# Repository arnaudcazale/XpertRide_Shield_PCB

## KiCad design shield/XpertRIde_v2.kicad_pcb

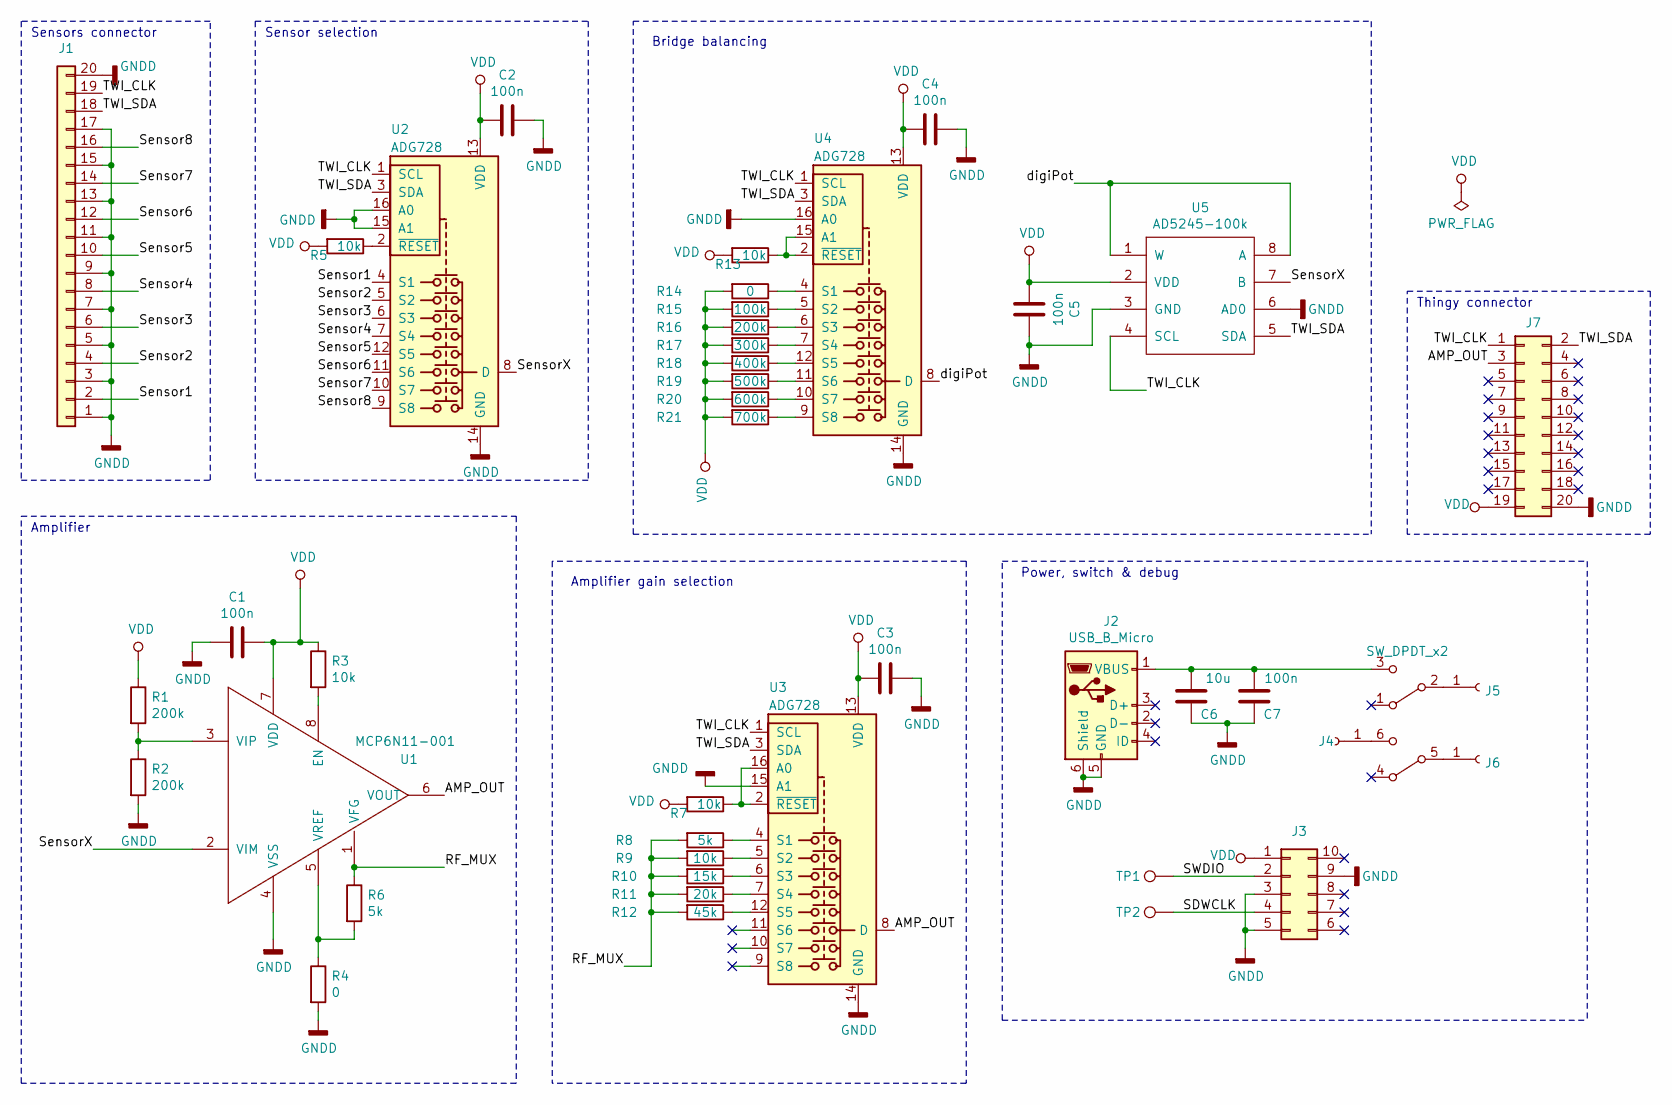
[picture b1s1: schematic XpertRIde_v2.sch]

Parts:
C1, C2, C3, C4, C5, C7: 100n; C_0402
C6: 10u; C_0603
J1: Conn_01x20; Samtec_ESHF_20
J2: USB_B_Micro; CUI_UJ2-MIBH-4-SMT-TR-67
J3: Conn_02x05_Counter_Clockwise; Tag_Connect_10
J4, J5, J6: Conn_01x01_Female; SolderWirePad_single_0-8mmDrill
J7: Conn_02x10_Odd_Even; Pin_Header_Straight_2x10_Pitch2.54mm
R1, R2, R16: 200k; R_0402
R3, R5, R7, R9, R13: 10k; R_0402
R4, R14: 0; R_0402
R6, R8: 5k; R_0402
R10: 15k; R_0402
R11: 20k; R_0402
R12: 45k; R_0402
R15: 100k; R_0402
R17: 300k; R_0402
R18: 400k; R_0402
R19: 500k; R_0402
R20: 600k; R_0402
R21: 700k; R_0402
SW1: SW_DPDT_x2; DPDT_IP67
TP1, TP2: TestPoint; Measurement_Point_Round-SMD-Pad_Small
U1: MCP6N11-001; SOIC-8_3.9x4.9mm_Pitch1.27mm
U2, U3, U4: ADG728; TSSOP-16_4.4x5mm_P0.65mm
U5: AD5245-100k; SOT-23-8

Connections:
/AMP_OUT: J7.3, U1.6 (VOUT), U3.8 (D)
/RF_MUX: R6.1, R8.2, R9.2, R10.2, R11.2, R12.2, U1.1 (VFG)
/SDWCLK: J3.4, TP2.1
/SWDIO: J3.2, TP1.1
/Sensor1: J1.2, U2.4 (S1)
/Sensor2: J1.4, U2.5 (S2)
/Sensor3: J1.6, U2.6 (S3)
/Sensor4: J1.8, U2.7 (S4)
/Sensor5: J1.10, U2.12 (S5)
/Sensor6: J1.12, U2.11 (S6)
/Sensor7: J1.14, U2.10 (S7)
/Sensor8: J1.16, U2.9 (S8)
/SensorX: U1.2 (VIM), U2.8 (D), U5.7 (B)
/TWI_CLK: J1.19, J7.1, U2.1 (SCL), U3.1 (SCL), U4.1 (SCL), U5.4 (SCL)
/TWI_SDA: J1.18, J7.2, U2.3 (SDA), U3.3 (SDA), U4.3 (SDA), U5.5 (SDA)
/digiPot: U4.8 (D), U5.1 (W), U5.8 (A)
GNDD: C1.2, C2.1, C3.1, C4.1, C5.1, C6.1, C7.1, J1.1, J1.3, J1.5, J1.7, J1.9, J1.11, J1.13, J1.15, J1.17, J1.20, J2.5 (GND), J2.6 (Shield), J3.3, J3.5, J3.9, J7.20, R2.2, R4.2, U1.4 (VSS), U2.14 (GND), U2.15 (A1), U2.16 (A0), U3.14 (GND), U3.15 (A1), U4.14 (GND), U4.16 (A0), U5.3 (GND), U5.6 (AD0)
unnamed: C6.2, C7.2, J2.1 (VBUS), SW1.3 (C)
unnamed: J4.1, SW1.6 (C)
unnamed: J5.1, SW1.2 (B)
unnamed: J6.1, SW1.5 (B)
unnamed: R1.2, R2.1, U1.3 (VIP)
unnamed: R3.2, U1.8 (EN)
unnamed: R4.1, R6.2, U1.5 (VREF)
unnamed: R5.1, U2.2 (~RESET)
unnamed: R7.1, U3.2 (~RESET), U3.16 (A0)
unnamed: R8.1, U3.4 (S1)
unnamed: R9.1, U3.5 (S2)
unnamed: R10.1, U3.6 (S3)
unnamed: R11.1, U3.7 (S4)
unnamed: R12.1, U3.12 (S5)
unnamed: R13.1, U4.2 (~RESET), U4.15 (A1)
unnamed: R14.1, U4.4 (S1)
unnamed: R15.1, U4.5 (S2)
unnamed: R16.1, U4.6 (S3)
unnamed: R17.1, U4.7 (S4)
unnamed: R18.1, U4.12 (S5)
unnamed: R19.1, U4.11 (S6)
unnamed: R20.1, U4.10 (S7)
unnamed: R21.1, U4.9 (S8)
VDD: C1.1, C2.2, C3.2, C4.2, C5.2, J3.1, J7.19, R1.1, R3.1, R5.2, R7.2, R13.2, R14.2, R15.2, R16.2, R17.2, R18.2, R19.2, R20.2, R21.2, U1.7 (VDD), U2.13 (VDD), U3.13 (VDD), U4.13 (VDD), U5.2 (VDD)

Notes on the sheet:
Bridge balancing
Amplifier
Amplifier gain selection
Sensors connector
Sensor selection
Power, switch & debug
Thingy connector

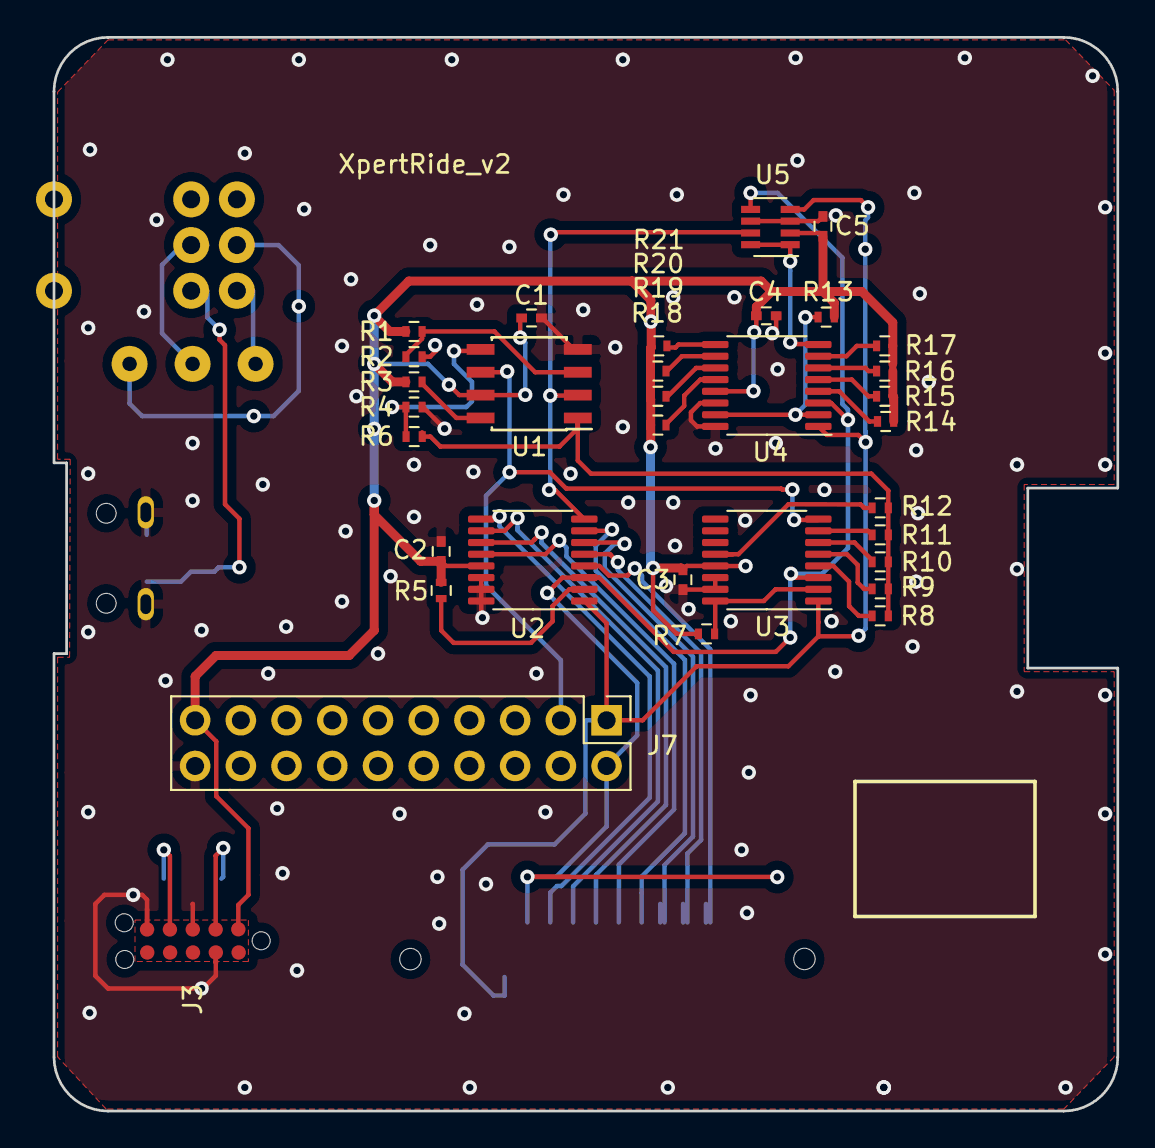
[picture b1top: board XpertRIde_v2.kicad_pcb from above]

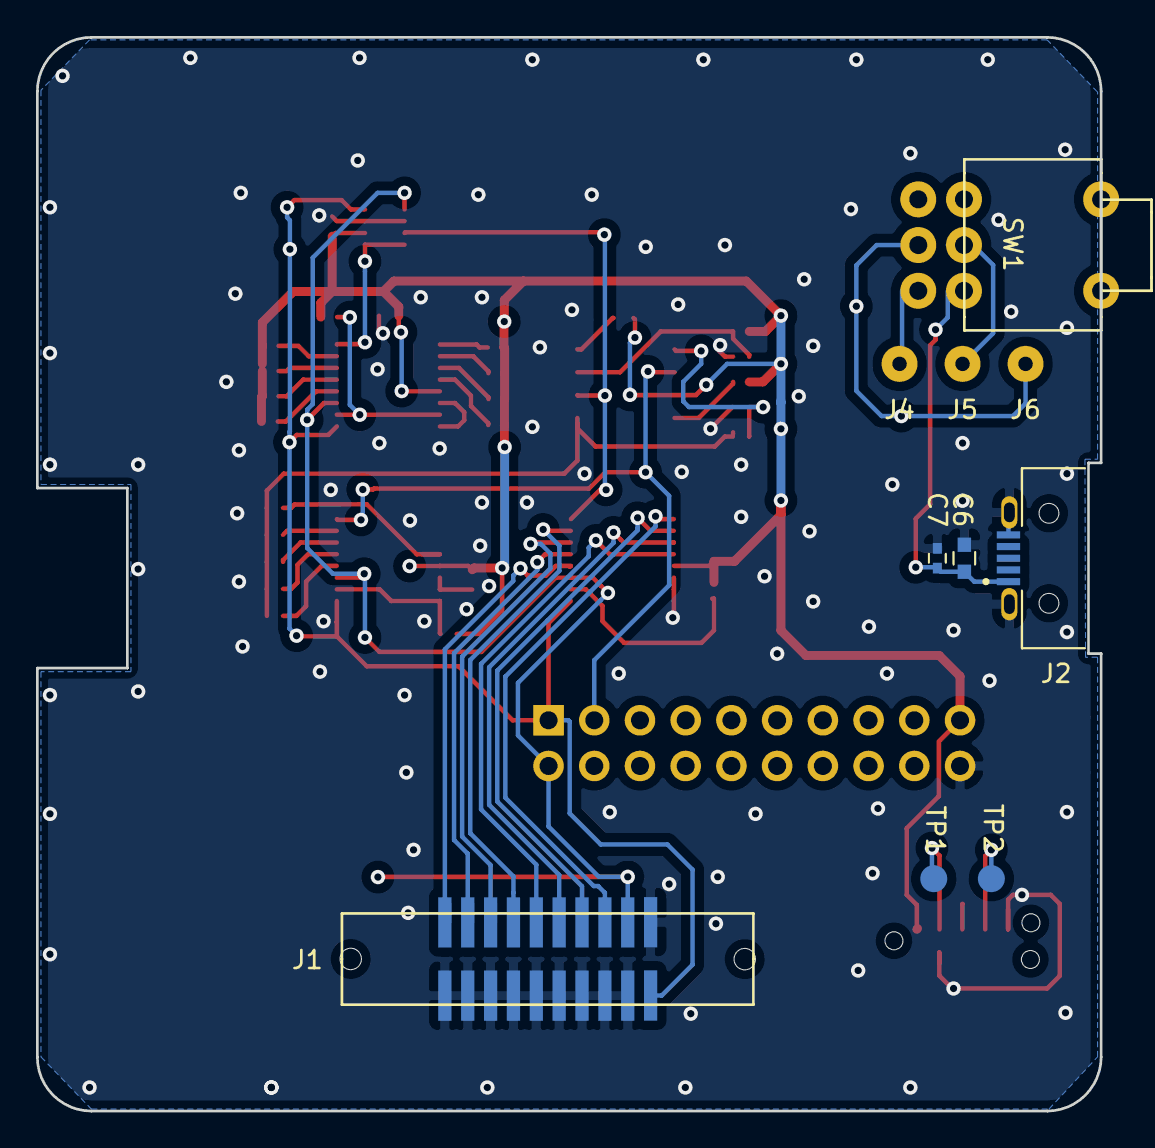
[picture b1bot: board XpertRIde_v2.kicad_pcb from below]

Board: 2 copper layers, 59.1 x 59.7 mm, 43 parts (10 on the bottom side), 41 nets.

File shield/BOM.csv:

Id;RÃ©fÃ©rence;BoÃ®tier;QuantitÃ©;DÃ©signation;RS;Samtec;mouser;qtité;
1;SW1;DPDT_IP67;1;SW_DPDT_x2;734-7356;;;30;ok
2;C1,C2,C3,C4,C5,C7;C_0402;6;100n;698-3207;;;180;ok
3;C6;C_0603;1;10u;846-7293;;;30;ok
4;J1;Samtec_ESHF_20 (mate = FFSD-10-01-N);1;Conn_01x20;196-9990;;;30;ok
5;R1,R2,R16;R_0402;3;200k;678-8945;;;90;ok
6;R3,R5,R7,R9,R13;R_0402;5;10k;812-1562;;;150;ok
7;R4,R14;R_0402;2;0R;393-2326;;;60;ok
8;R6,R8;R_0402;2;5k;678-9409;;;60;ok
9;R10;R_0402;1;15k;134-6344;;;30;ok
10;R11;R_0402;1;20k;678-8958;;;30;ok
11;R12;R_0402;1;45k;701-5453;;;30;ok
12;R15;R_0402;1;100k;678-4684;;;30;ok
13;R17;R_0402;1;300k;807-2211;;;30;ok
14;R18;R_0402;1;400k;678-9305;;;30;ok
15;R19;R_0402;1;500k;678-9412;;;30;ok
16;R20;R_0402;1;600k;678-9481;;;30;ok
17;R21;R_0402;1;700k;678-9566;;;30;ok
18;U1;SOIC-8_3.9x4.9mm_Pitch1.27mm;1;MCP6N11-001;755-9546;;;30;ok
19;U2,U3,U4;TSSOP-16_4.4x5mm_P0.65mm;3;ADG728;538-8349;;;90;ok
20;U5;SOT-23-8;1;AD5245-100k;759-0718;;;30;ok
21;J2;CUI_UJ2-MIBH-4-SMT-TR-67;1;USB_B_Micro;;;490-UJ2-MIBH4SMTTR67;30;
22;J7;Samtec_ZW_10-08-F-D-350-070;1;Conn_02x10_Odd_Even;;Samtec_ZW_10-08-F-D-350-070;;30;

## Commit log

2020-04-22 main PCB OK
2020-04-22 support OK
2020-04-24 3D sandwich
2020-04-27 new design
2020-05-02 MOdif_size
2020-05-04 new PCB dimensions
2020-05-06 modif dimensions-joint
2020-05-06 3D files
2020-06-02 fixed switch position
